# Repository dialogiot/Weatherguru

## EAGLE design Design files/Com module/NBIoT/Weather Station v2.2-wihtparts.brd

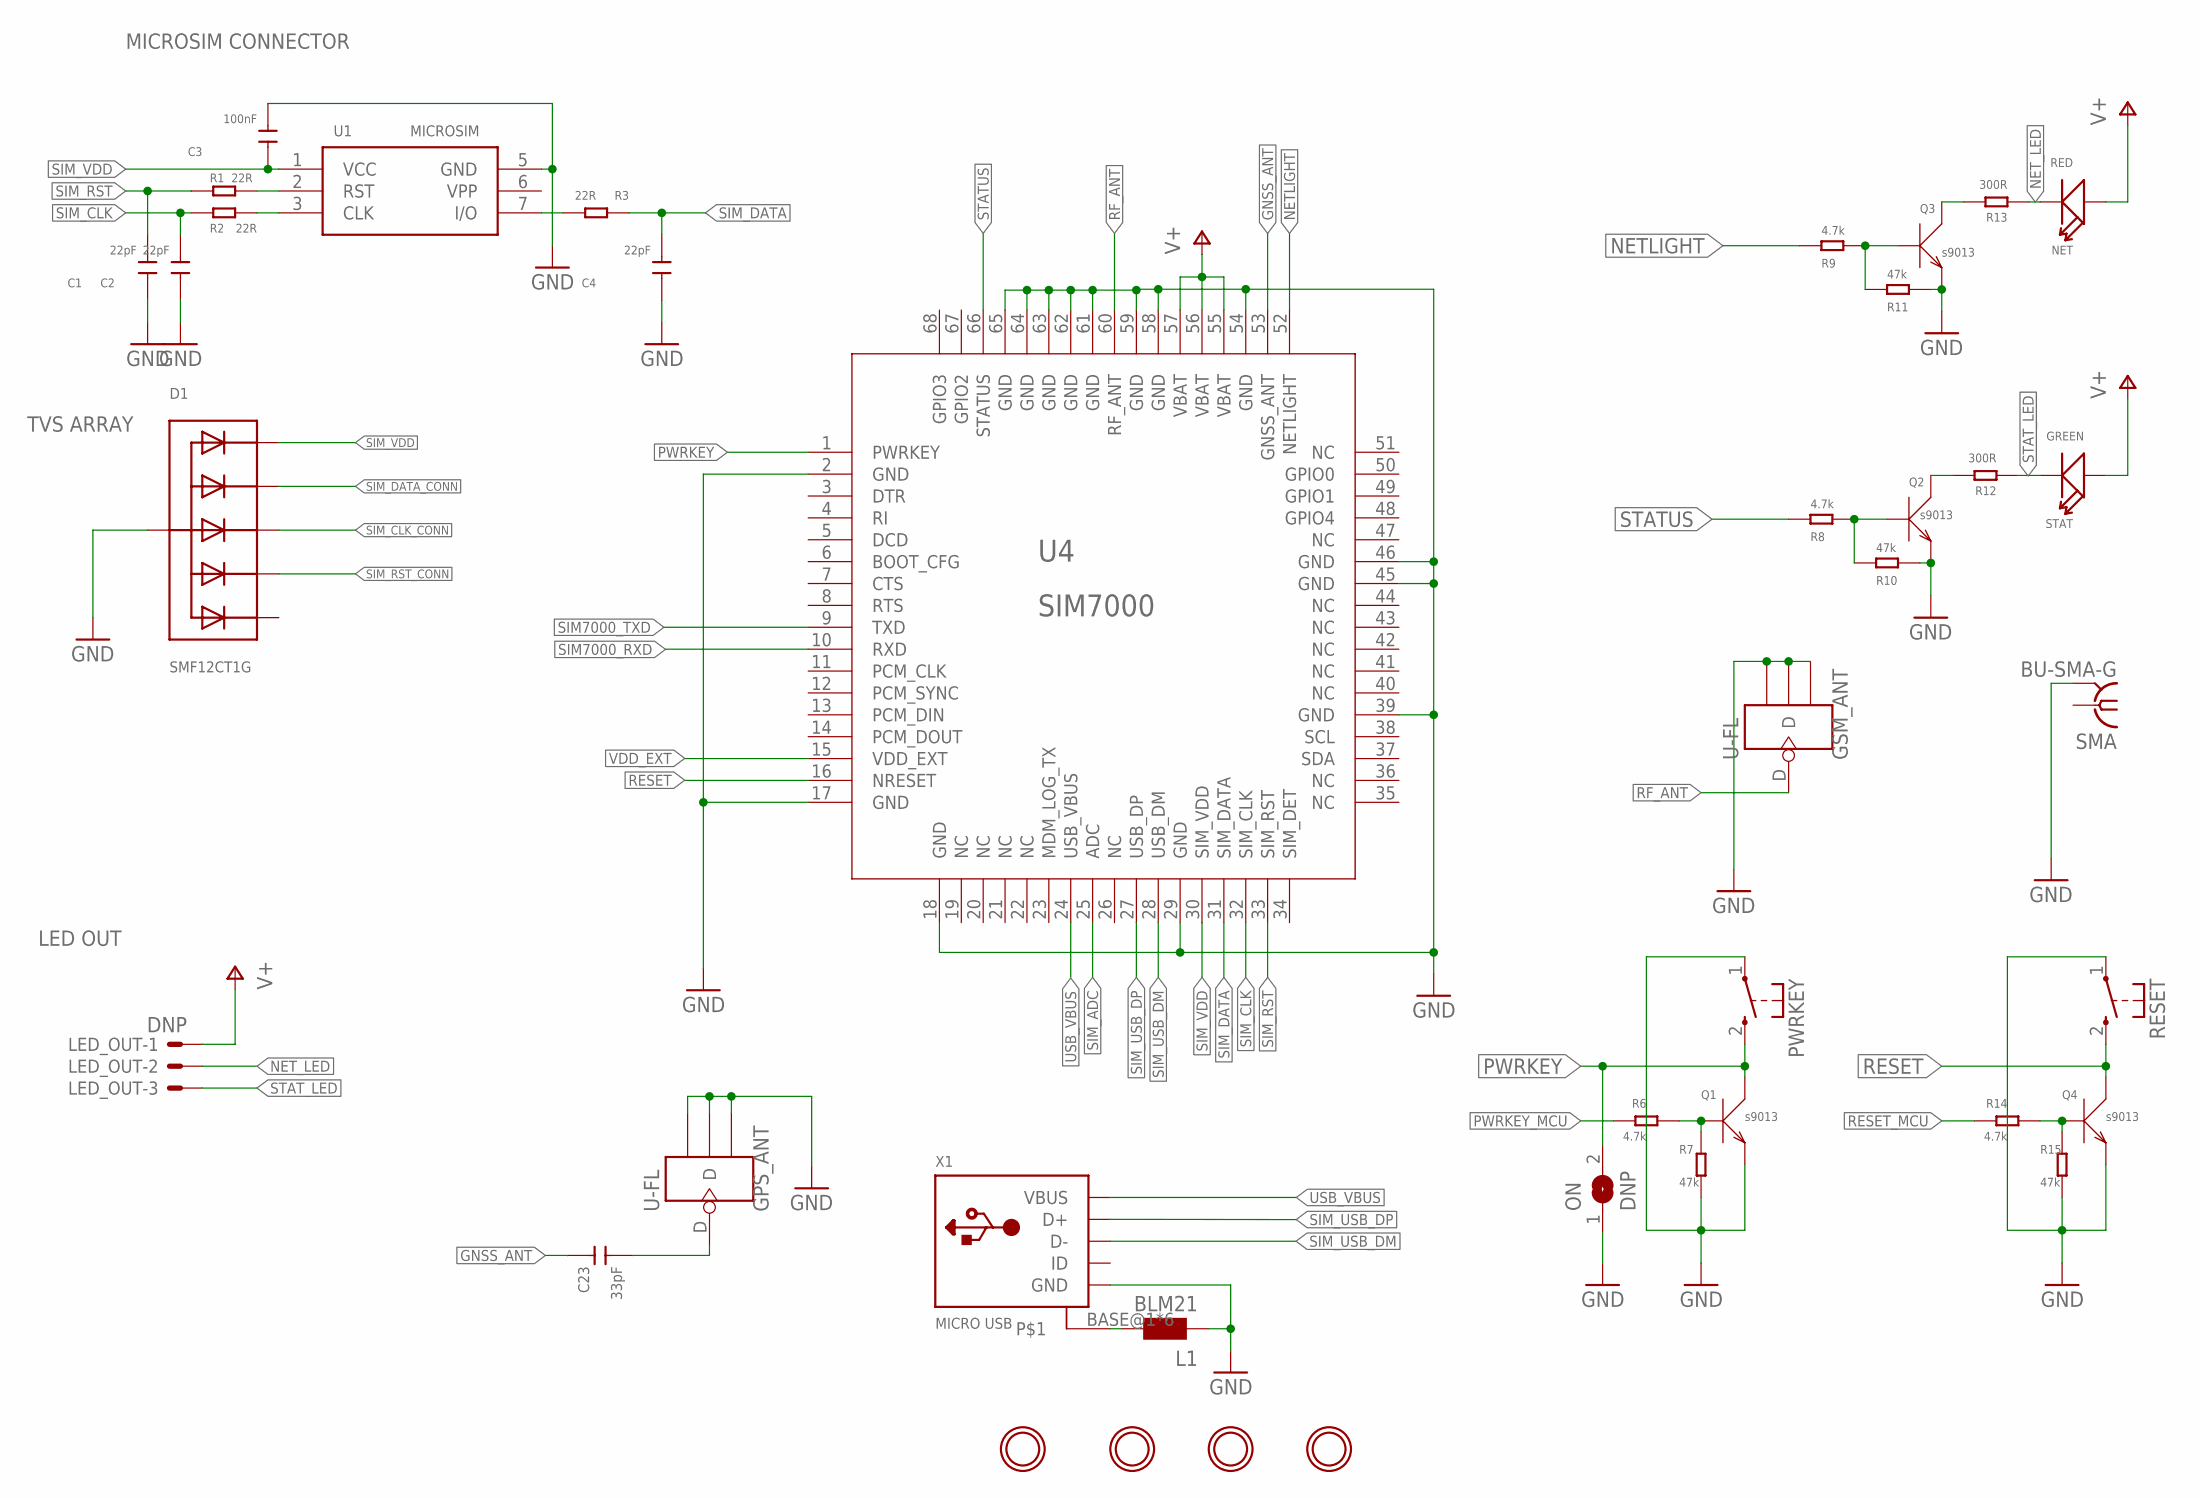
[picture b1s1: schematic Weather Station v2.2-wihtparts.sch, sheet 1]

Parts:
$H1, $H2, $H3, $H4: DNP; MOUNTINGHOLE_3.0_PLATEDTHIN
C1, C2, C4: 22pF; 0805; MPN C0402C220J5GACTU
C3: 100nF; 0805; MPN 08053G105ZAT2A
C23: 33pF; 0805
D1: SMF12CT1G; SOT363; MPN SMF12CT1G
GPS_ANT: U-FL; 4P-U-FL
GSM_ANT: U-FL; 4P-U-FL; MPN U.FL-R-SMT(01)
L1: BLM21; 0805; MPN BLM21AG121SN1D
LED_OUT: DNP; JST-XH-03-WIRE
NET: RED; LED-2P-2.54-3MM; MPN 5988110107F
ON: DNP; SOLDERJUMPER_REFLOW
PWRKEY: KSS-2EG4430
Q1, Q2, Q3, Q4: s9013; SOT23; MPN DTC143TKAT146.
R1, R2, R3: 22R; 0805; MPN CRM0805-FX-51R0ELF
R6, R8, R9, R14: 4.7k; 0805; MPN MCWF08P4701FTL
R7, R10, R11, R15: 47k; 0805; MPN CRCW080547K0FKEA
R12, R13: 300R; 0805; MPN ERA-6AEB301V
RESET: KSS-2EG4430
SMA: BU-SMA-G; MPN 19-49-5-TGG
STAT: GREEN; LED-2P-2.54-3MM; MPN SML-LX0805SUGC-TR
U1: MICROSIM
U4: SIM7000
X1: MICRO USB; 4UCONN_20329_V2; MPN 10118193-0001LF

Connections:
GND: C1.1, C2.1, C3.2, C4.1, D1.2 (A), GPS_ANT.GND1, GPS_ANT.GND2, GPS_ANT.GND3, GSM_ANT.GND1, GSM_ANT.GND2, GSM_ANT.GND3, L1.1, ON.1, PWRKEY.1, Q1.2 (E), Q2.2 (E), Q3.2 (E), Q4.2 (E), R7.2, R10.2, R11.2, R15.2, RESET.1, SMA.2, SMA.3 (2), SMA.4 (2), SMA.5 (2), U1.5 (GND), U4.2 (GND), U4.17 (GND), U4.18 (GND), U4.29 (GND), U4.39 (GND), U4.45 (GND), U4.46 (GND), U4.54 (GND), U4.58 (GND), U4.59 (GND), U4.61 (GND), U4.62 (GND), U4.63 (GND), U4.64 (GND), U4.65 (GND), X1.GND; also elsewhere on the board
GNSS_ANT: C23.2, U4.53 (GNSS_ANT)
GPIO2: U4.67 (GPIO2)
GPIO3: U4.68 (GPIO3)
unnamed: Q4.1 (B), R14.2, R15.1
unnamed: Q2.3 (C), R12.2
unnamed: Q2.1 (B), R8.2, R10.1
unnamed: Q3.3 (C), R13.2
unnamed: Q3.1 (B), R9.2, R11.1
unnamed: C23.1, GPS_ANT.D
unnamed: L1.2, X1.BASE@1, X1.BASE@2, X1.SPRT@1, X1.SPRT@2, X1.SPRT@3, X1.SPRT@4
unnamed: Q1.1 (B), R6.2, R7.1
NETLIGHT: R9.1, U4.52 (NETLIGHT)
NET_LED: LED_OUT.2, NET.K (-), R13.1
PWRKEY: ON.2, PWRKEY.2 (S), Q1.3 (C), U4.1 (PWRKEY)
PWRKEY_MCU: R6.1; also elsewhere on the board
RESET: Q4.3 (C), RESET.2 (S), U4.16 (NRESET)
RESET_MCU: R14.1; also elsewhere on the board
RF_ANT: GSM_ANT.D, U4.60 (RF_ANT)
SIM7000_RXD: U4.10 (RXD); also elsewhere on the board
SIM7000_TXD: U4.9 (TXD); also elsewhere on the board
SIM_ADC: U4.25 (ADC)
SIM_CLK: C2.2, R2.2, U4.32 (SIM_CLK)
SIM_CLK_CONN: D1.4 (C3), R2.1, U1.3 (CLK)
SIM_DATA: C4.2, R3.1, U4.31 (SIM_DATA)
SIM_DATA_CONN: D1.3 (C2), R3.2, U1.7 (I/O)
SIM_RST: C1.2, R1.2, U4.33 (SIM_RST)
SIM_RST_CONN: D1.5 (C4), R1.1, U1.2 (RST)
SIM_USB_DM: U4.28 (USB_DM), X1.D-
SIM_USB_DP: U4.27 (USB_DP), X1.D+
SIM_VDD: C3.1, D1.1 (C1), U1.1 (VCC), U4.30 (SIM_VDD)
STATUS: R8.1, U4.66 (STATUS)
STAT_LED: LED_OUT.3, R12.1, STAT.K (-)
USB_VBUS: U4.24 (USB_VBUS), X1.VBUS
V+: LED_OUT.1, NET.A (+), STAT.A (+), U4.55 (VBAT), U4.56 (VBAT), U4.57 (VBAT); also elsewhere on the board
VDD_EXT: U4.15 (VDD_EXT); also elsewhere on the board

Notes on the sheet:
TVS ARRAY
MICROSIM CONNECTOR
LED OUT

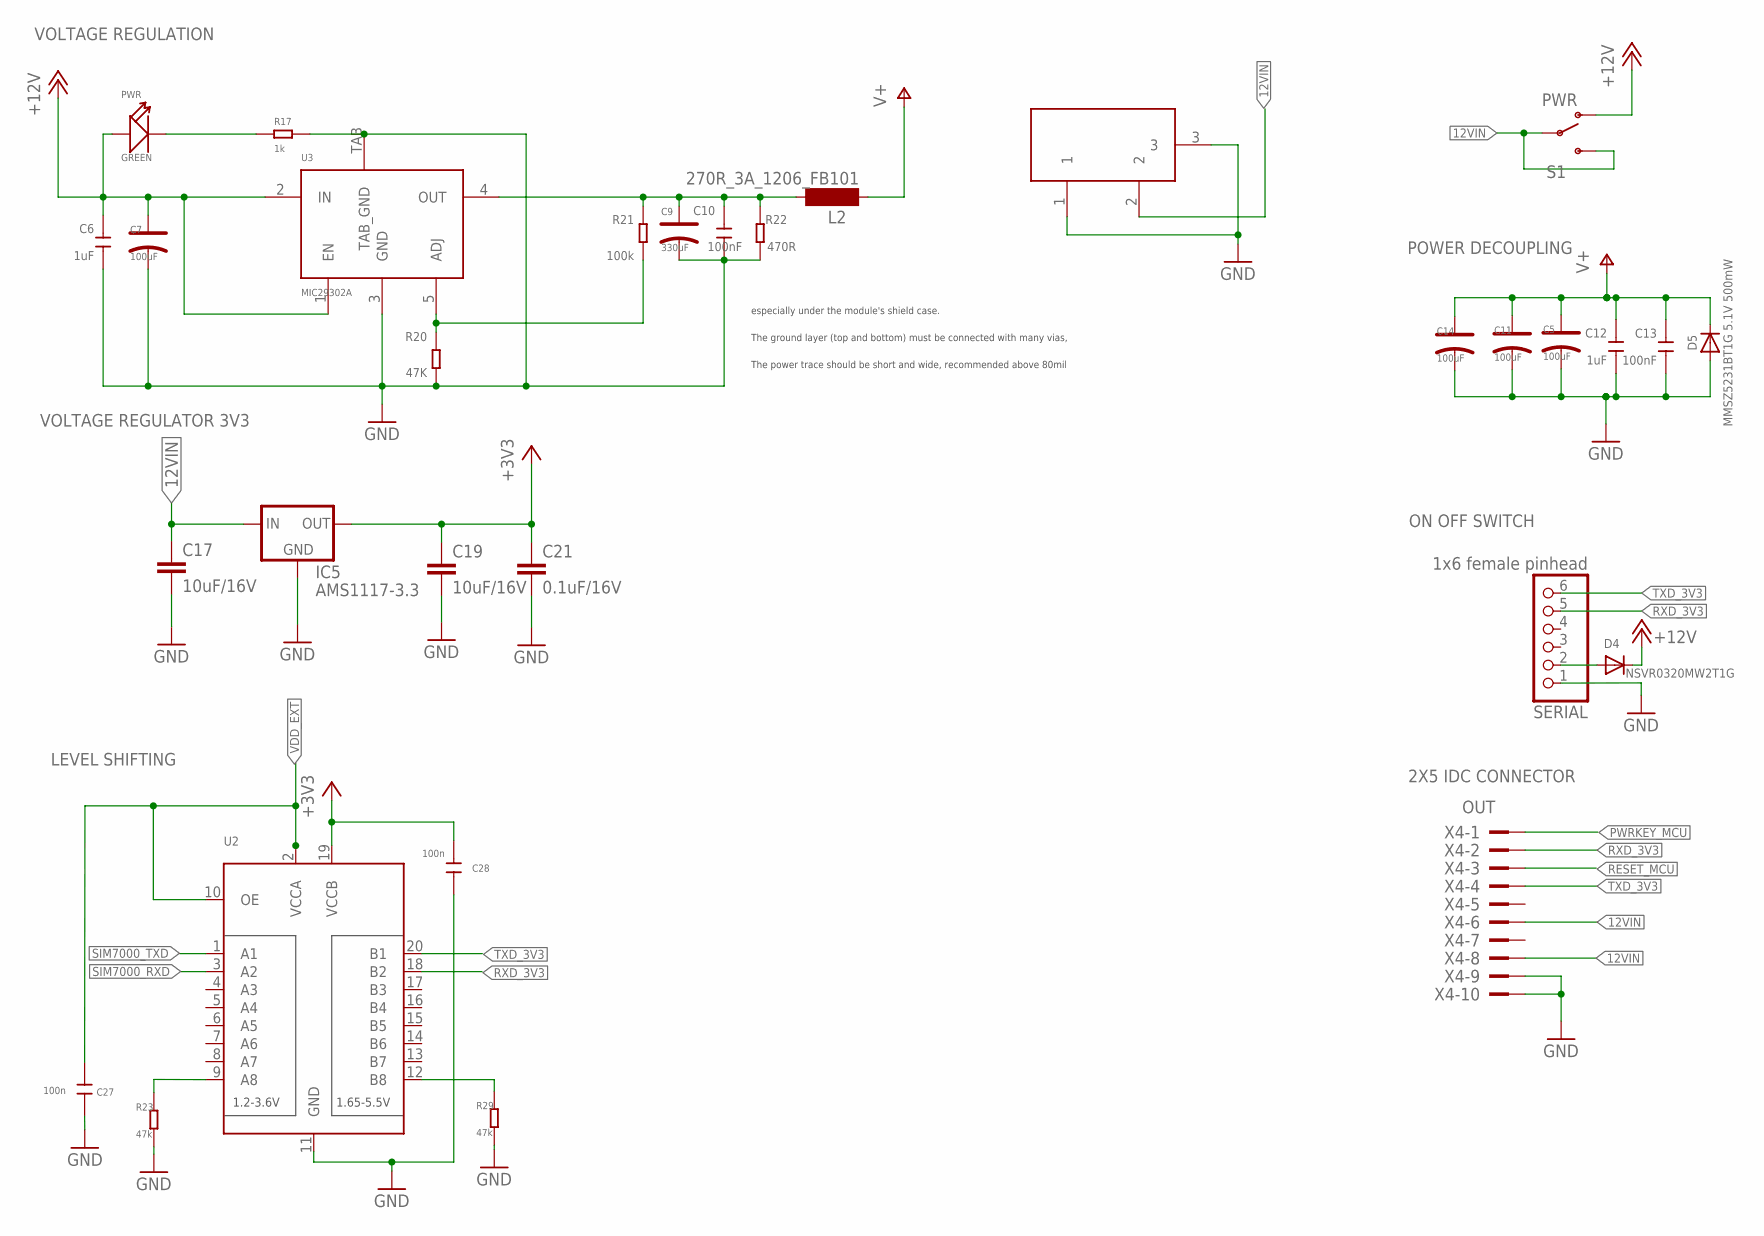
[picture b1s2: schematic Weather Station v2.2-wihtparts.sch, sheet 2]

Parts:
C5, C7, C11, C14: 100uF; AVX_D; MPN TCJD107M025R0055
C6: 1uF; 0805; MPN 08053G105ZAT2A
C8: DC21MMX; DC-21MM; MPN FC681478
C9: 330uF; AVX_D; MPN TCJE337M016R0050
C10: 100nF; 0805; MPN MC0805B104M160CT
C12: 1uF; 0805; MPN GRM21BF51C106ZE15L
C13: 100nF; 0805; MPN 08055A330JAT2A
C17, C19: 10uF/16V; C0805K
C21: 0.1uF/16V; C0805K
C27, C28: 100n; 0805
D4: NSVR0320MW2T1G; SOD-323; MPN NSVR0320MW2T1G
D5: MMSZ5231BT1G 5.1V 500mW; SOD-123; MPN MMSZ5231BT1G
IC5: AMS1117-3.3; SOT223
L2: 270R_3A_1206_FB101; SM-1206; MPN 742792121
PWR: GREEN; D0805; MPN SML-LX0805SUGC-TR
R17: 1k; 0805; MPN CRCW08051K00FKTA
R20: 47K; 0805; MPN CRCW080543K0JNEA.
R21: 100k; 0805; MPN CRCW0805100KJNEA
R22: 470R; 0805; MPN ERA-6AEB471V
R23, R29: 47k; 0805
S1: PWR; SWITCH-SPDT-CUSTOM; MPN EG1201
SERIAL: 1x6 female pinhead; 1X06
U2: TXB0108PWR; TSSOP20
U3: MIC29302A; TO-263A; MPN MIC29302WU-TR
X4: OUT; PAK100/2500-10; MPN 30310-6002HB

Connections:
12VIN: C8.2, C17.1, IC5.3 (IN), S1.2, S1.3 (S), X4.6, X4.8
+3V3: C19.1, C21.1, C28.2, IC5.2 (OUT), U2.19 (VCCB)
+12V: C6.2, C7.+, D4.C, PWR.+, S1.1 (O), U3.1 (EN), U3.2 (IN)
GND: C5.-, C6.1, C7.-, C8.1, C8.3, C9.-, C10.1, C11.-, C12.1, C13.1, C14.-, C17.2, C19.2, C21.2, C27.1, C28.1, D5.A, IC5.1 (GND), R17.2, R20.1, R22.1, R23.2, R29.2, SERIAL.1, U2.11 (GND), U3.3 (GND), U3.TAB (TAB_GND), X4.9, X4.10; also elsewhere on the board
unnamed: R20.2, R21.1, U3.5 (ADJ)
unnamed: R23.1, U2.9 (A8)
unnamed: D4.A, SERIAL.2
unnamed: R29.1, U2.12 (B8)
unnamed: PWR.-, R17.1
PWRKEY_MCU: X4.1; also elsewhere on the board
RESET_MCU: X4.3; also elsewhere on the board
RXD_3V3: SERIAL.5, U2.18 (B2), X4.2
SIM7000_RXD: U2.3 (A2); also elsewhere on the board
SIM7000_TXD: U2.1 (A1); also elsewhere on the board
TXD_3V3: SERIAL.6, U2.20 (B1), X4.4
V+: C5.+, C11.+, C12.2, C13.2, C14.+, D5.C, L2.1; also elsewhere on the board
VDD_EXT: C27.2, U2.2 (VCCA), U2.10 (OE); also elsewhere on the board
VOUT: C9.+, C10.2, L2.2, R21.2, R22.2, U3.4 (OUT)

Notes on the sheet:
The power trace should be short and wide, recommended above 80mil
The ground layer (top and bottom) must be connected with many vias,
especially under the module's shield case.
VOLTAGE REGULATION
ON OFF SWITCH
POWER DECOUPLING
LEVEL SHIFTING
2X5 IDC CONNECTOR
VOLTAGE REGULATOR 3V3

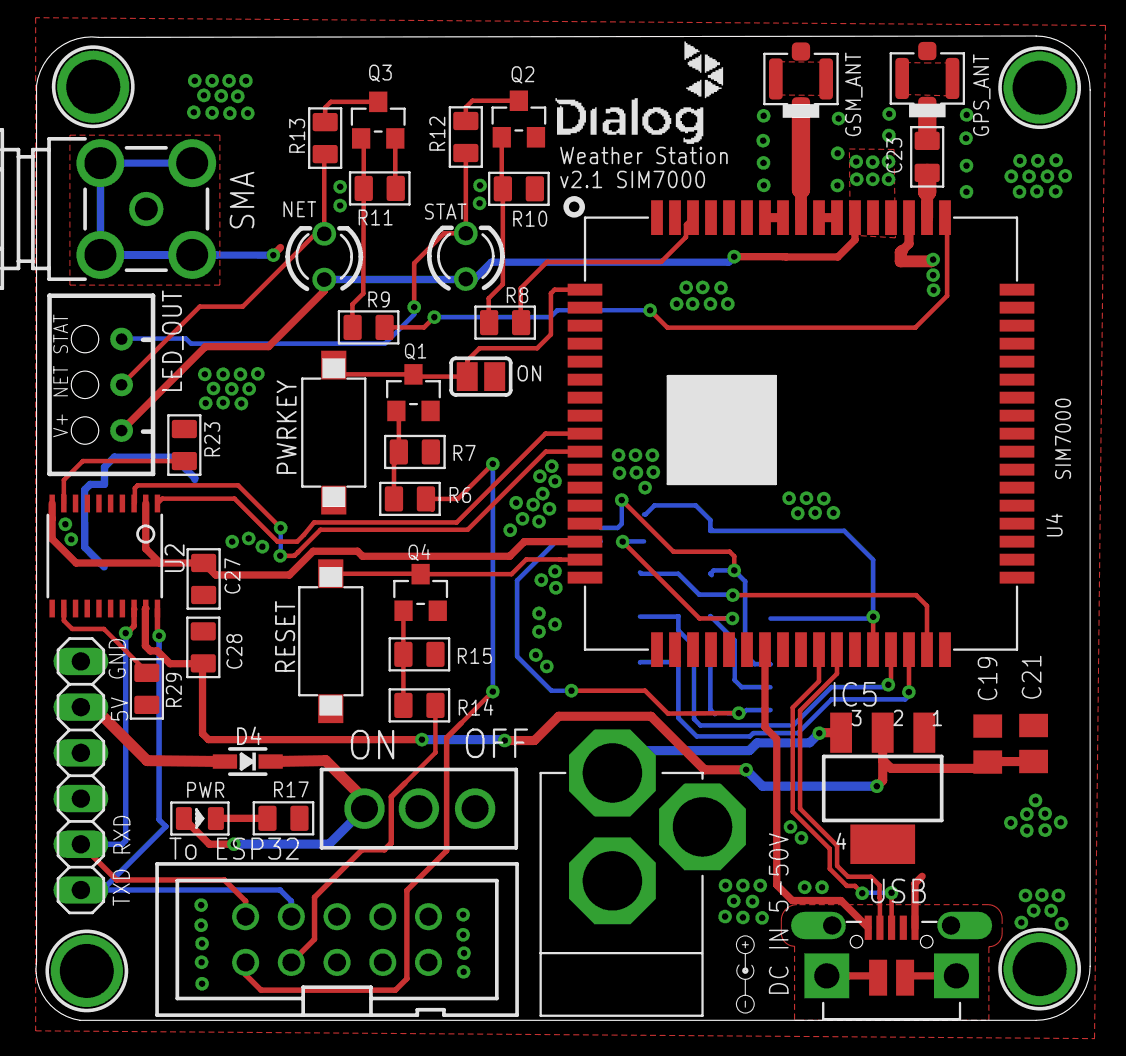
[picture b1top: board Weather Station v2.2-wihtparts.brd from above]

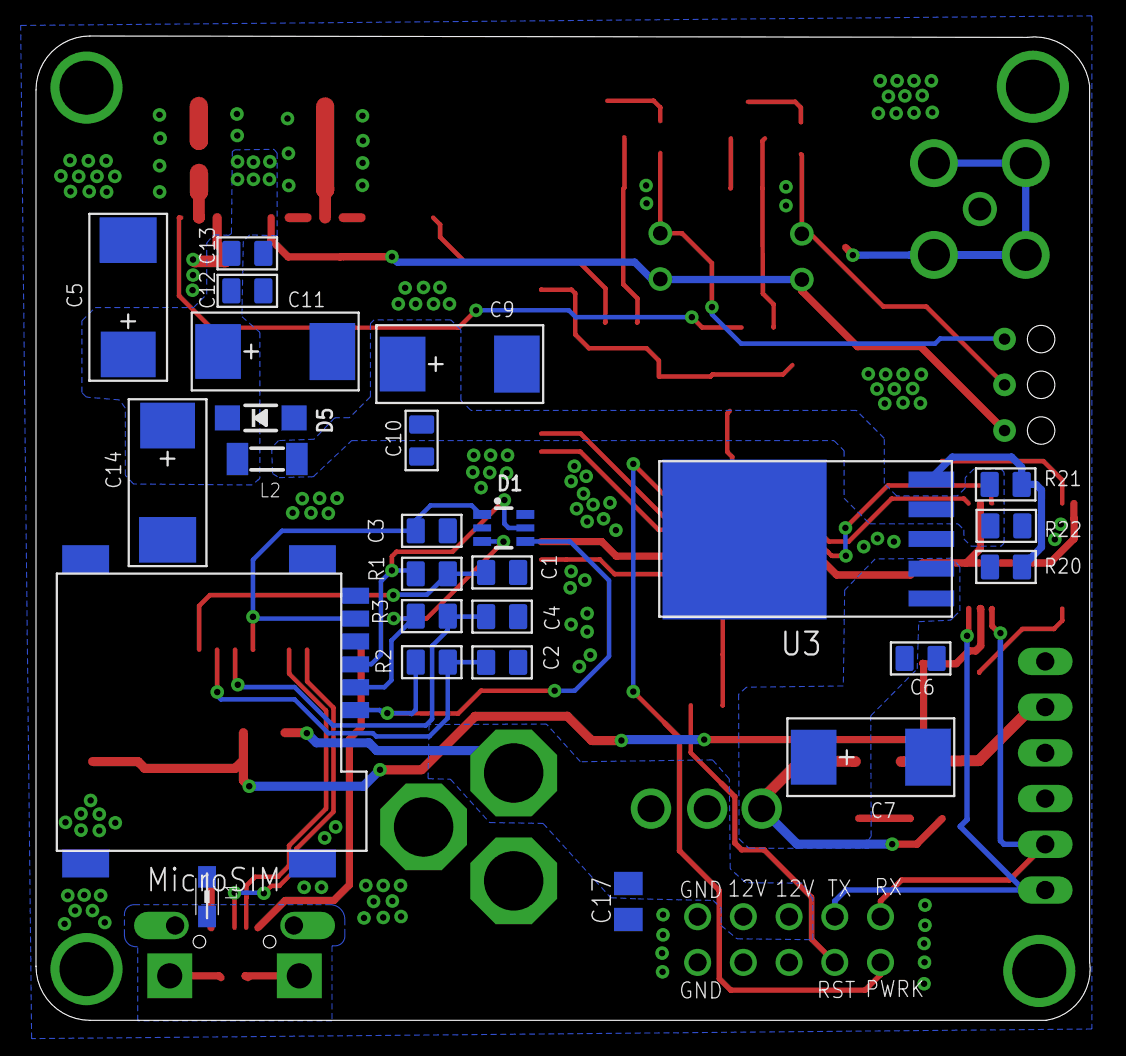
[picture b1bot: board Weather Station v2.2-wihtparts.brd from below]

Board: 2 copper layers, 58.6 x 54.7 mm, 71 parts (26 on the bottom side), 44 nets.

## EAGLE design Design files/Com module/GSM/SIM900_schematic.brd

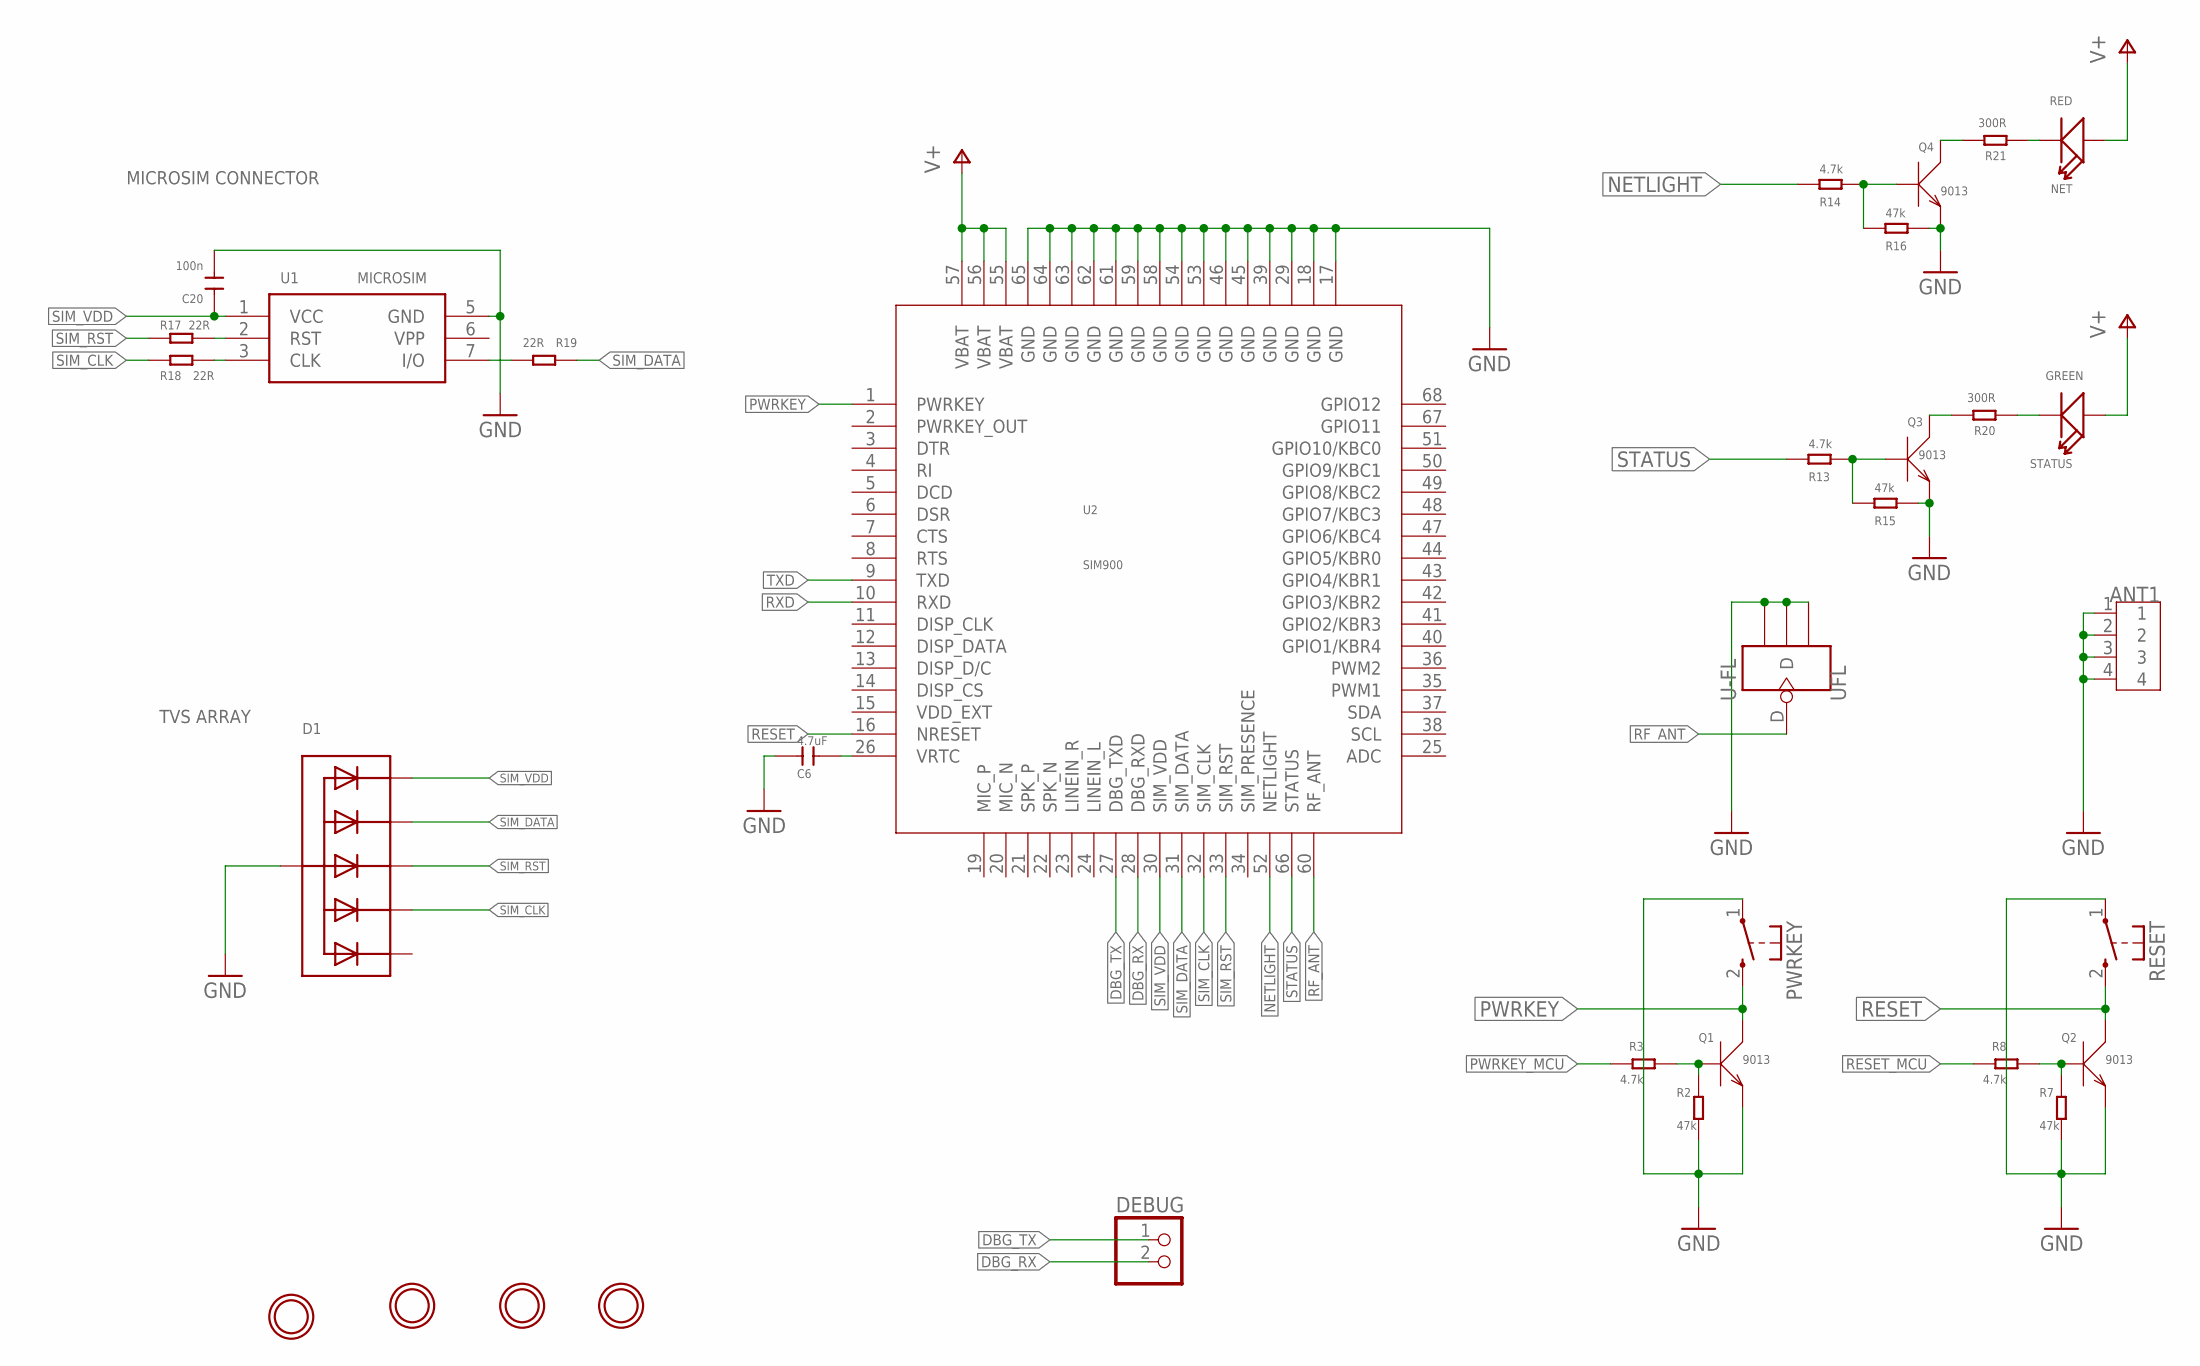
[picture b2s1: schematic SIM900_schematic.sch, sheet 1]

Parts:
ANT1: ANTENNA-SMA-IPX; SMA-TO-IPX
C6: 4.7uF; 0805
C20: 100n; 0805
D1: TVSARRAY_5LANE; SOT363
DEBUG: PINHD-1X2; 1X02
NET: RED; LED-0805
PWRKEY: KSS-2EG4430
Q1, Q2, Q3, Q4: 9013; SOT23
R2, R7, R15, R16: 47k; 0805
R3, R8, R13, R14: 4.7k; 0805
R17, R18, R19: 22R; 0805
R20, R21: 300R; 0805
RESET: KSS-2EG4430
STATUS: GREEN; LED-0805
U1: MICROSIM
U2: SIM900
U$1, U$2, U$3, U$4: MOUNTINGHOLE3.0THIN; MOUNTINGHOLE_3.0_PLATEDTHIN
UFL: U-FL; 4P-U-FL

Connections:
DBG_RX: DEBUG.2, U2.28 (DBG_RXD)
DBG_TX: DEBUG.1, U2.27 (DBG_TXD)
GND: ANT1.1, ANT1.2, ANT1.3, ANT1.4, C6.1, C20.2, D1.2 (A), PWRKEY.1, Q1.2 (E), Q2.2 (E), Q3.2 (E), Q4.2 (E), R2.2, R7.2, R15.2, R16.2, RESET.1, U1.5 (GND), U2.17 (GND), U2.18 (GND), U2.29 (GND), U2.39 (GND), U2.45 (GND), U2.46 (GND), U2.53 (GND), U2.54 (GND), U2.58 (GND), U2.59 (GND), U2.61 (GND), U2.62 (GND), U2.63 (GND), U2.64 (GND), U2.65 (GND), UFL.GND1, UFL.GND2, UFL.GND3; also elsewhere on the board
unnamed: Q2.1 (B), R7.1, R8.2
unnamed: Q3.3 (C), R20.2
unnamed: R19.2, U1.7 (I/O)
unnamed: R18.1, U1.3 (CLK)
unnamed: R17.1, U1.2 (RST)
unnamed: R20.1, STATUS.-
unnamed: Q3.1 (B), R13.2, R15.1
unnamed: Q4.3 (C), R21.2
unnamed: NET.-, R21.1
unnamed: Q4.1 (B), R14.2, R16.1
unnamed: Q1.1 (B), R2.1, R3.2
NETLIGHT: R14.1, U2.52 (NETLIGHT)
PWRKEY: PWRKEY.2 (S), Q1.3 (C), U2.1 (PWRKEY)
PWRKEY_MCU: R3.1; also elsewhere on the board
RESET: Q2.3 (C), RESET.2 (S), U2.16 (NRESET)
RESET_MCU: R8.1; also elsewhere on the board
RF_ANT: U2.60 (RF_ANT), UFL.D
RXD: U2.10 (RXD); also elsewhere on the board
SIM_CLK: D1.5 (C4), R18.2, U2.32 (SIM_CLK)
SIM_DATA: D1.3 (C2), R19.1, U2.31 (SIM_DATA)
SIM_RST: D1.4 (C3), R17.2, U2.33 (SIM_RST)
SIM_VDD: C20.1, D1.1 (C1), U1.1 (VCC), U2.30 (SIM_VDD)
STATUS: R13.1, U2.66 (STATUS)
TXD: U2.9 (TXD); also elsewhere on the board
V+: NET.+, STATUS.+, U2.55 (VBAT), U2.56 (VBAT), U2.57 (VBAT); also elsewhere on the board
VRTC: C6.2, U2.26 (VRTC)

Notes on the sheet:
TVS ARRAY
MICROSIM CONNECTOR

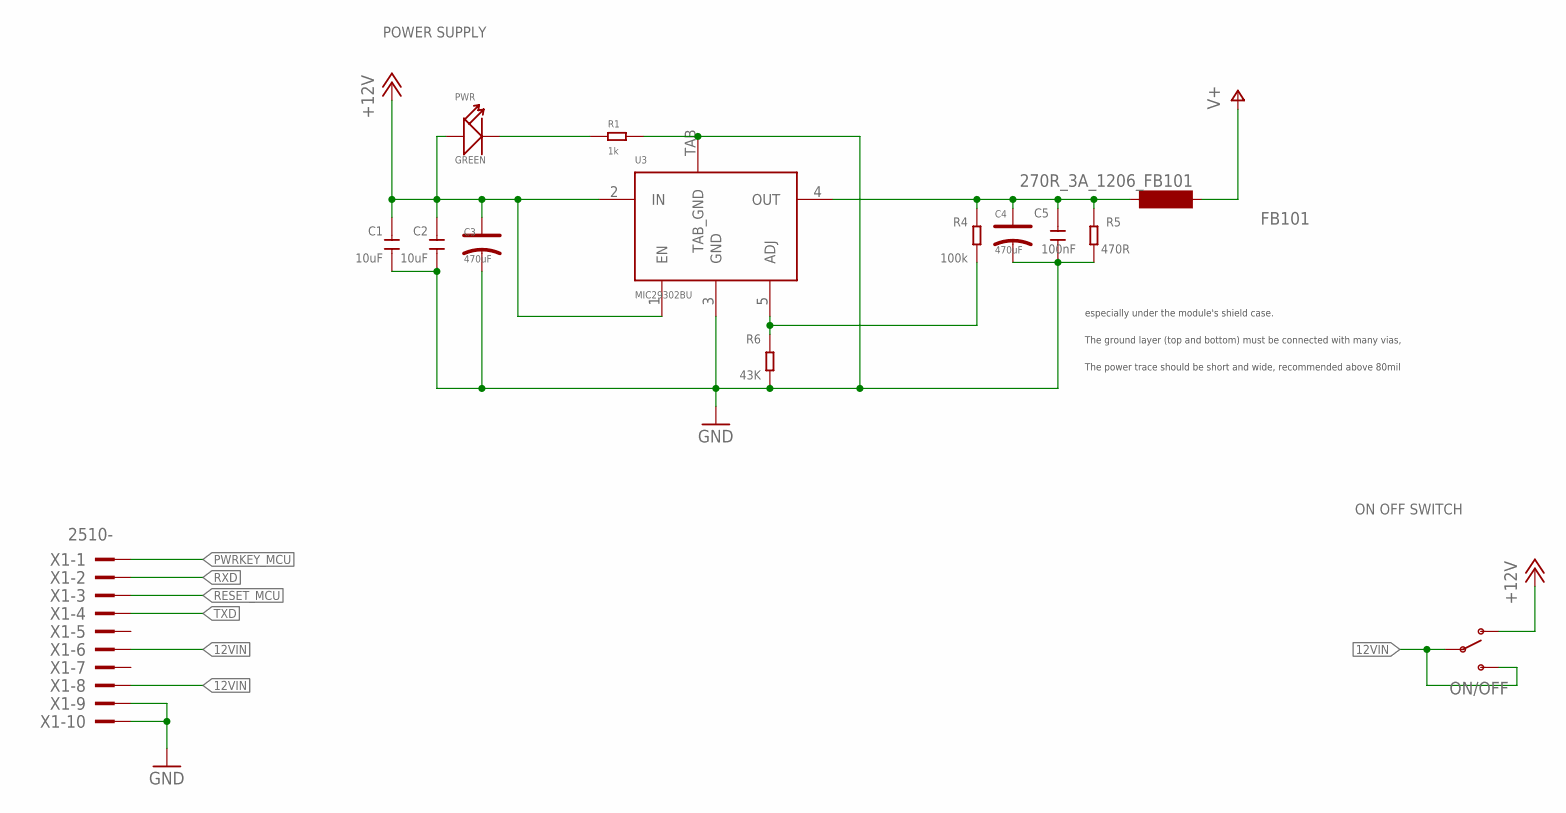
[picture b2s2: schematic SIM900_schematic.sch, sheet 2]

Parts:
C1, C2: 10uF; 0805
C3, C4: 470uF; AVX_D
C5: 100nF; 0805
FB101: 270R_3A_1206_FB101; SM-1206
ON/OFF: SWITCH-SPDTPTH; SWITCH-SPDT
PWR: GREEN; D0805
R1: 1k; 0805
R4: 100k; 0805
R5: 470R; 0805
R6: 43K; 0805
U3: MIC29302BU; TO-263
X1: 2510-; PAK100/2500-10

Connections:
12VIN: ON/OFF.2, ON/OFF.3 (S), X1.6, X1.8
+12V: C1.2, C2.2, C3.+, ON/OFF.1 (O), PWR.+, U3.1 (EN), U3.2 (IN)
GND: C1.1, C2.1, C3.-, C4.-, C5.1, R1.2, R5.1, R6.1, U3.3 (GND), U3.TAB (TAB_GND), X1.9, X1.10; also elsewhere on the board
unnamed: R4.1, R6.2, U3.5 (ADJ)
unnamed: PWR.-, R1.1
PWRKEY_MCU: X1.1; also elsewhere on the board
RESET_MCU: X1.3; also elsewhere on the board
RXD: X1.2; also elsewhere on the board
TXD: X1.4; also elsewhere on the board
V+: FB101.1; also elsewhere on the board
VOUT: C4.+, C5.2, FB101.2, R4.2, R5.2, U3.4 (OUT)

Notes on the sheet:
The power trace should be short and wide, recommended above 80mil
The ground layer (top and bottom) must be connected with many vias,
especially under the module's shield case.
POWER SUPPLY
ON OFF SWITCH

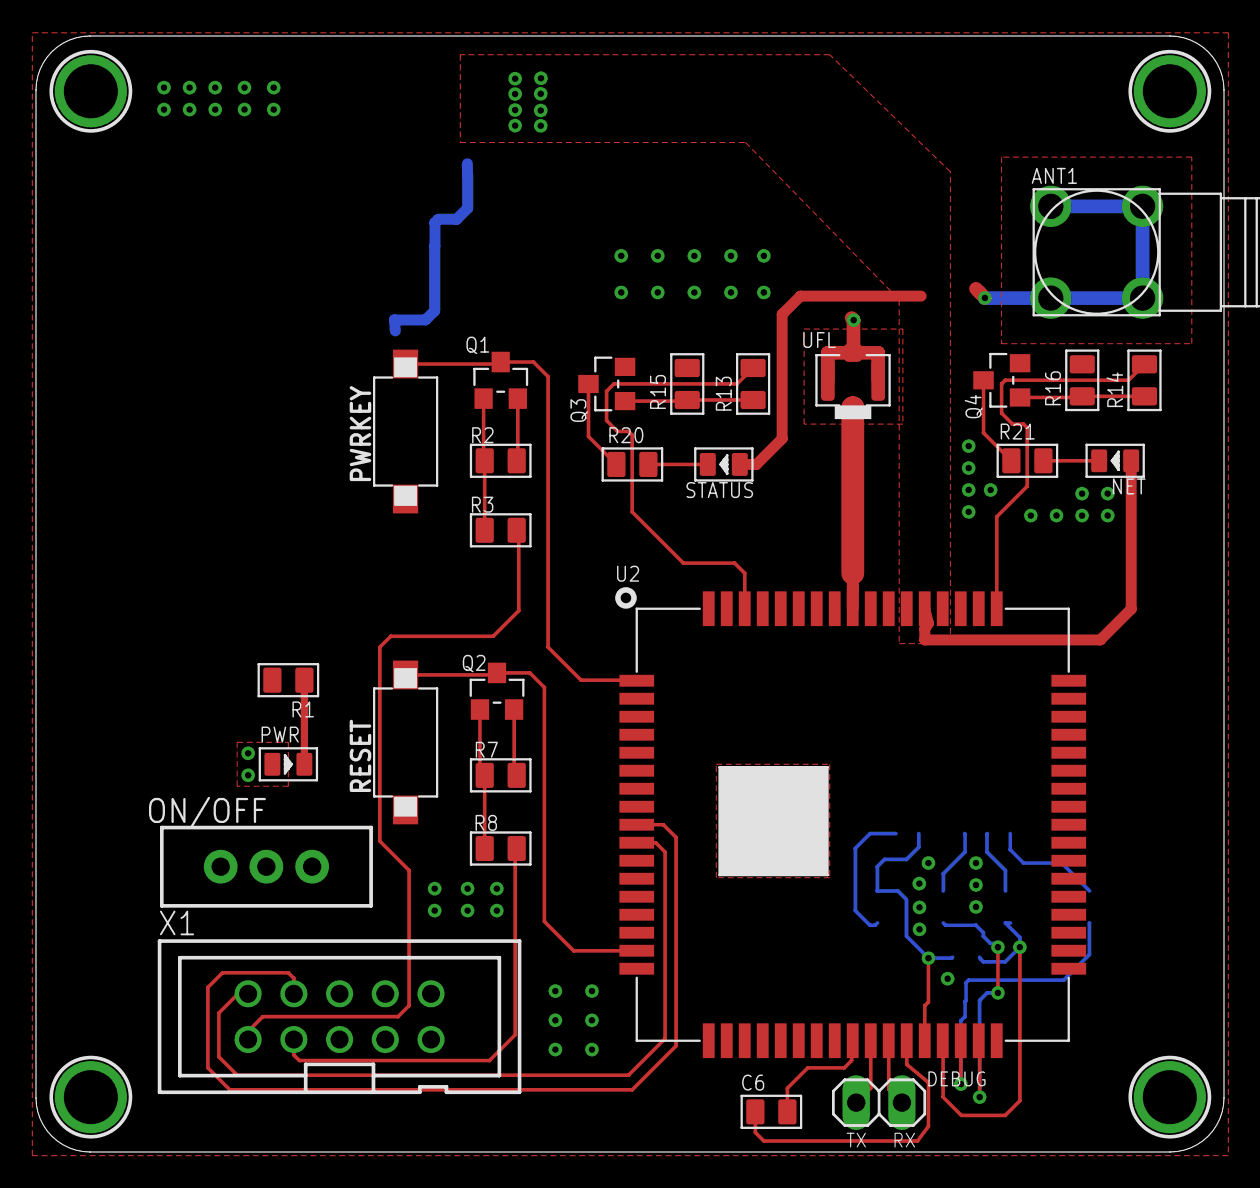
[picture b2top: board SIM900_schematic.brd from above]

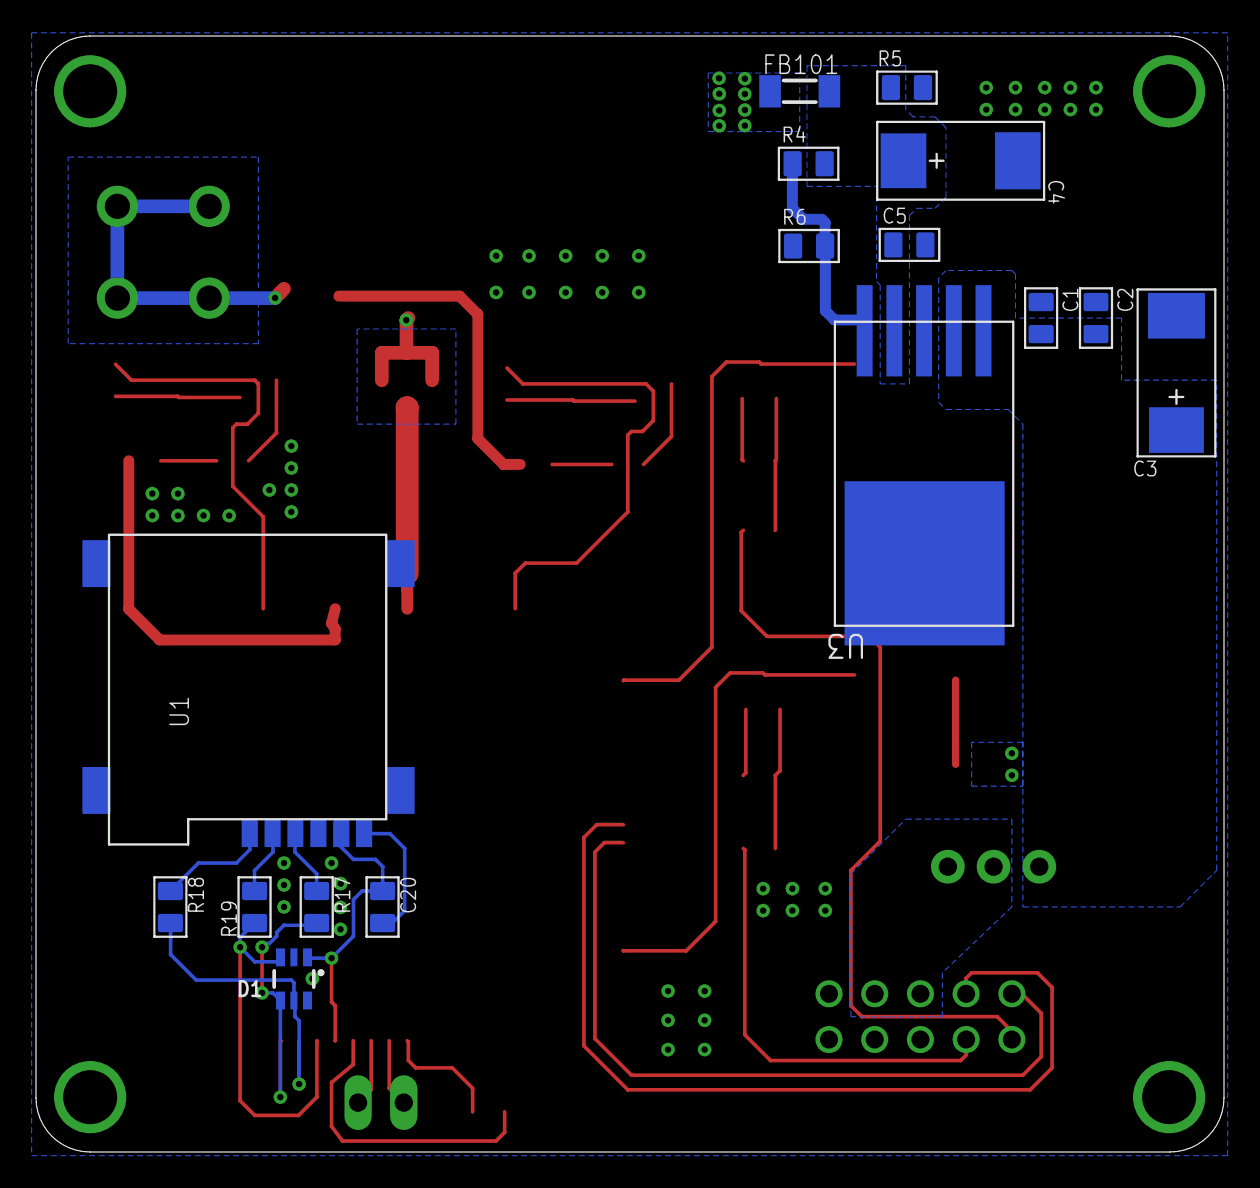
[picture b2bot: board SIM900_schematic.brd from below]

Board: 2 copper layers, 66.0 x 62.0 mm, 47 parts (16 on the bottom side), 34 nets.

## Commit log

2019-03-18 3/18/2019
    Commit
2019-03-18 18/3/2019
    Commit
2019-03-18 18/2/2019
    Commit

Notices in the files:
parts and their libraries:
SparkFun-Electromechanical: Licensing: Creative Commons ShareAlike 4.0 International - https://creativecommons.org/licenses/by-sa/4.0
